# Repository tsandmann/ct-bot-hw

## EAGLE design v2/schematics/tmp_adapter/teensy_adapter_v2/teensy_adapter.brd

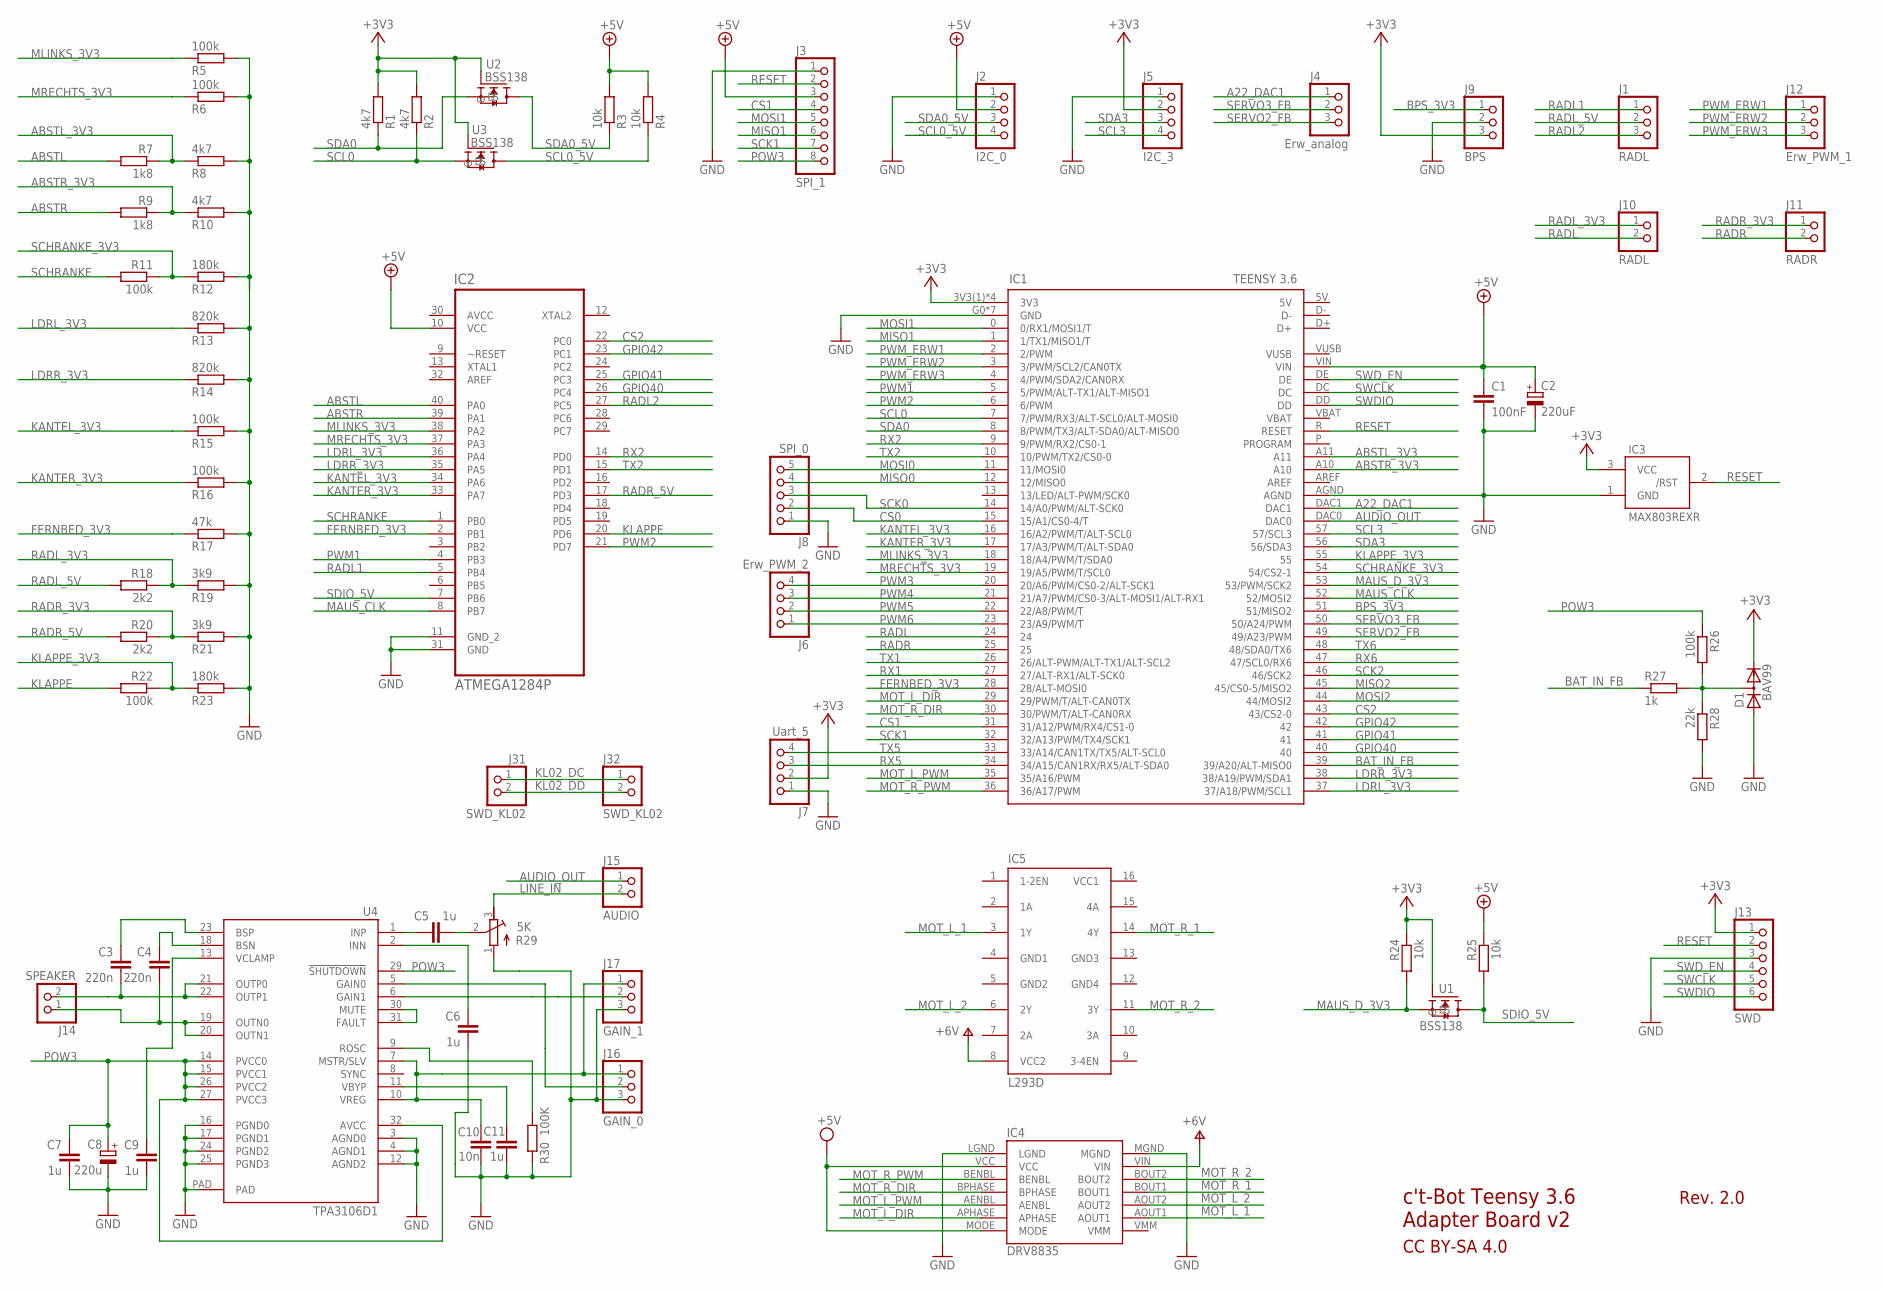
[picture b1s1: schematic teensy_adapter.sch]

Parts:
C1: 100nF; C025-025X050
C2: 220uF; E2,5-6
C3, C4: 220n; C025-025X050
C5, C6, C7, C9, C11: 1u; C025-025X050
C8: 220u; E2,5-6
C10: 10n; C025-025X050
D1: BAV99; SOT23
IC1: TEENSY 3.6; T36
IC2: ATMEGA1284P; DIP254P1524X483-40
IC3: MAX803REXR; SC70-3L
IC4: DRV8835; POLOLU_MOTOR_DRV_DRV8835
IC5: L293D; DIL16
J1: RADL; 1X03
J2: I2C_0; 1X04
J3: SPI_1; 1X08
J4: Erw_analog; 1X03
J5: I2C_3; 1X04
J6: Erw_PWM_2; 1X04
J7: Uart_5; 1X04
J8: SPI_0; 1X05
J9: BPS; 1X03
J10: RADL; 1X02
J11: RADR; 1X02
J12: Erw_PWM_1; 1X03
J13: SWD; 1X06
J14: SPEAKER; 1X02
J15: AUDIO; 1X02
J16: GAIN_0; 1X03
J17: GAIN_1; 1X03
J31: SWD_KL02; 1X02
J32: SWD_KL02; 1X02/90
R1, R2, R8, R10: 4k7; 0204V
R3, R4, R24, R25: 10k; 0204V
R5, R6, R11, R15, R16, R22, R26: 100k; 0204V
R7, R9: 1k8; 0204V
R12, R23: 180k; 0204V
R13, R14: 820k; 0204V
R17: 47k; 0204V
R18, R20: 2k2; 0204V
R19, R21: 3k9; 0204V
R27: 1k; 0204V
R28: 22k; 0204V
R29: 5K; RTRIM64W
R30: 100K; 0204V
U1, U2, U3: BSS138
U4: TPA3106D1; HTQFP32

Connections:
+3V3: D1.2 (C), IC1.3V3(1) (3V3), IC1.3V3(2) (3V3), IC1.3V3(3) (3V3), IC1.3V3(4) (3V3), IC3.3 (VCC), J5.2, J7.2, J9.3, J13.1, R1.2, R2.2, R24.1, U1.G, U2.G, U3.G
+5V: C1.1, C2.+, IC1.VIN, IC2.10 (VCC), IC4.MODE, IC4.VCC, J2.2, J3.3, R3.2, R4.2, R25.1
+6V: IC4.VIN, IC5.8 (VCC2)
A22_DAC1: IC1.DAC1, J4.1
ABSTL: IC2.40 (PA0), R7.2
ABSTL_3V3: IC1.A11, R7.1, R8.1
ABSTR: IC2.39 (PA1), R9.2
ABSTR_3V3: IC1.A10, R9.1, R10.1
AUDIO_OUT: IC1.DAC0, J15.1
AVCC: IC2.30 (AVCC)
BAT_IN_FB: IC1.39 (39/A20/ALT-MISO0), R27.1
BPS_3V3: IC1.51 (51/MISO2), J9.1
BSN: C4.1, U4.18 (BSN)
BSP: C3.1, U4.23 (BSP)
CS0: IC1.15 (15/A1/CS0-4/T), J8.2
CS1: IC1.31 (31/A12/PWM/RX4/CS1-0), J3.4
CS2: IC1.43 (43/CS2-0), IC2.22 (PC0)
FERNBED_3V3: IC1.28 (28/ALT-MOSI0), IC2.2 (PB1), R17.1
GAIN0: J16.2, U4.5 (GAIN0)
GAIN1: J17.2, U4.6 (GAIN1)
GND: C1.2, C2.-, C6.2, C7.2, C8.-, C9.2, C10.2, C11.2, D1.1 (A), IC1.AGND, IC1.G0 (GND), IC1.G1 (GND), IC1.G2 (GND), IC1.G3 (GND), IC1.G4 (GND), IC1.G5 (GND), IC1.G6 (GND), IC2.11 (GND_2), IC2.31 (GND), IC3.1 (GND), IC4.LGND, IC4.MGND, J2.1, J3.1, J5.1, J7.1, J8.1, J9.2, J13.3, J16.3, J17.3, R5.2, R6.2, R8.2, R10.2, R12.2, R13.2, R14.2, R15.2, R16.2, R17.2, R19.2, R21.2, R23.2, R28.2, R29.1 (E), R30.1, U4.3 (AGND0), U4.4 (AGND1), U4.12 (AGND2), U4.16 (PGND0), U4.17 (PGND1), U4.24 (PGND2), U4.25 (PGND3), U4.PAD
GND1: IC5.4 (GND1)
GND2: IC5.5 (GND2)
GND3: IC5.13 (GND3)
GND4: IC5.12 (GND4)
GPIO40: IC1.40, IC2.26 (PC4)
GPIO41: IC1.41, IC2.25 (PC3)
GPIO42: IC1.42, IC2.23 (PC1)
INN: C6.1, U4.2 (INN)
INP: C5.1, U4.1 (INP)
KANTEL_3V3: IC1.16 (16/A2/PWM/T/ALT-SCL0), IC2.34 (PA6), R15.1
KANTER_3V3: IC1.17 (17/A3/PWM/T/ALT-SDA0), IC2.33 (PA7), R16.1
KL02_DC: J31.1, J32.1
KL02_DD: J31.2, J32.2
KLAPPE: IC2.20 (PD6), R22.2
KLAPPE_3V3: IC1.55, R22.1, R23.1
LDRL_3V3: IC1.37 (37/A18/PWM/SCL1), IC2.36 (PA4), R13.1
LDRR_3V3: IC1.38 (38/A19/PWM/SDA1), IC2.35 (PA5), R14.1
LINE_IN: J15.2, R29.3 (A)
MAUS_CLK: IC1.52 (52/MOSI2), IC2.8 (PB7)
MAUS_D_3V3: IC1.53 (53/PWM/SCK2), R24.2, U1.S
MISO0: IC1.12 (12/MISO0), J8.4
MISO1: IC1.1 (1/TX1/MISO1/T), J3.6
MISO2: IC1.45 (45/CS0-5/MISO2)
MLINKS_3V3: IC1.18 (18/A4/PWM/T/SDA0), IC2.38 (PA2), R5.1
MOSI0: IC1.11 (11/MOSI0), J8.5
MOSI1: IC1.0 (0/RX1/MOSI1/T), J3.5
MOSI2: IC1.44 (44/MOSI2)
MOT_L_1: IC4.AOUT1, IC5.3 (1Y)
MOT_L_2: IC4.AOUT2, IC5.6 (2Y)
MOT_L_DIR: IC1.29 (29/PWM/T/ALT-CAN0TX), IC4.APHASE
MOT_L_PWM: IC1.35 (35/A16/PWM), IC4.AENBL
MOT_R_1: IC4.BOUT1, IC5.14 (4Y)
MOT_R_2: IC4.BOUT2, IC5.11 (3Y)
MOT_R_DIR: IC1.30 (30/PWM/T/ALT-CAN0RX), IC4.BPHASE
MOT_R_PWM: IC1.36 (36/A17/PWM), IC4.BENBL
MRECHTS_3V3: IC1.19 (19/A5/PWM/T/SCL0), IC2.37 (PA3), R6.1
unnamed: D1.3 (AC), R26.2, R27.2, R28.1
unnamed: U4.30 (MUTE), U4.31 (FAULT)
unnamed: C5.2, R29.2 (S)
OUTN: C4.2, J14.1, U4.19 (OUTN0), U4.20 (OUTN1)
OUTP: C3.2, J14.2, U4.21 (OUTP0), U4.22 (OUTP1)
POW3: C7.1, C8.+, J3.8, R26.1, U4.14 (PVCC0), U4.15 (PVCC1), U4.26 (PVCC2), U4.27 (PVCC3), U4.29 (!SHUTDOWN), U4.32 (AVCC)
PWM1: IC1.5 (5/PWM/ALT-TX1/ALT-MISO1), IC2.4 (PB3)
PWM2: IC1.6 (6/PWM), IC2.21 (PD7)
PWM3: IC1.20 (20/A6/PWM/CS0-2/ALT-SCK1), J6.4
PWM4: IC1.21 (21/A7/PWM/CS0-3/ALT-MOSI1/ALT-RX1), J6.3
PWM5: IC1.22 (22/A8/PWM/T), J6.2
PWM6: IC1.23 (23/A9/PWM/T), J6.1
PWM_ERW1: IC1.2 (2/PWM), J12.1
PWM_ERW2: IC1.3 (3/PWM/SCL2/CAN0TX), J12.2
PWM_ERW3: IC1.4 (4/PWM/SDA2/CAN0RX), J12.3
RADL: IC1.24, J10.2
RADL1: IC2.5 (PB4), J1.1
RADL2: IC2.27 (PC5), J1.3
RADL_3V3: J10.1, R18.1, R19.1
RADL_5V: J1.2, R18.2
RADR: IC1.25, J11.2
RADR_3V3: J11.1, R20.1, R21.1
RADR_5V: IC2.17 (PD3), R20.2
RESET: IC1.R (RESET), IC3.2 (/RST), J3.2, J13.2
ROSC: R30.2, U4.9 (ROSC)
RX1: IC1.27 (27/ALT-RX1/ALT-SCK0)
RX2: IC1.9 (9/PWM/RX2/CS0-1), IC2.14 (PD0)
RX5: IC1.34 (34/A15/CAN1RX/RX5/ALT-SDA0), J7.3
RX6: IC1.47 (47/SCL0/RX6)
SCHRANKE: IC2.1 (PB0), R11.2
SCHRANKE_3V3: IC1.54 (54/CS2-1), R11.1, R12.1
SCK0: IC1.14 (14/A0/PWM/ALT-SCK0), J8.3
SCK1: IC1.32 (32/A13/PWM/TX4/SCK1), J3.7
SCK2: IC1.46 (46/SCK2)
SCL0: IC1.7 (7/PWM/RX3/ALT-SCL0/ALT-MOSI0), R2.1, U3.S
SCL0_5V: J2.4, R4.1, U3.D
SCL3: IC1.57 (57/SCL3), J5.4
SDA0: IC1.8 (8/PWM/TX3/ALT-SDA0/ALT-MISO0), R1.1, U2.S
SDA0_5V: J2.3, R3.1, U2.D
SDA3: IC1.56 (56/SDA3), J5.3
SDIO_5V: IC2.7 (PB6), R25.2, U1.D
SERVO2_FB: IC1.49 (49/A23/PWM), J4.3
SERVO3_FB: IC1.50 (50/A24/PWM), J4.2
SWCLK: IC1.DC, J13.5
SWDIO: IC1.DD, J13.6
SWD_EN: IC1.DE, J13.4
TX1: IC1.26 (26/ALT-PWM/ALT-TX1/ALT-SCL2)
TX2: IC1.10 (10/PWM/TX2/CS0-0), IC2.15 (PD1)
TX5: IC1.33 (33/A14/CAN1TX/TX5/ALT-SCL0), J7.4
TX6: IC1.48 (48/SDA0/TX6)
VBYP: C11.1, U4.11 (VBYP)
VCC1: IC5.16 (VCC1)
VCLAMP: C9.1, U4.13 (VCLAMP)
VREG: C10.1, J16.1, J17.1, U4.7 (MSTR/SLV), U4.10 (VREG)

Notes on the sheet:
c't-Bot Teensy 3.6 Adapter Board v2
Rev. 2.0
CC BY-SA 4.0

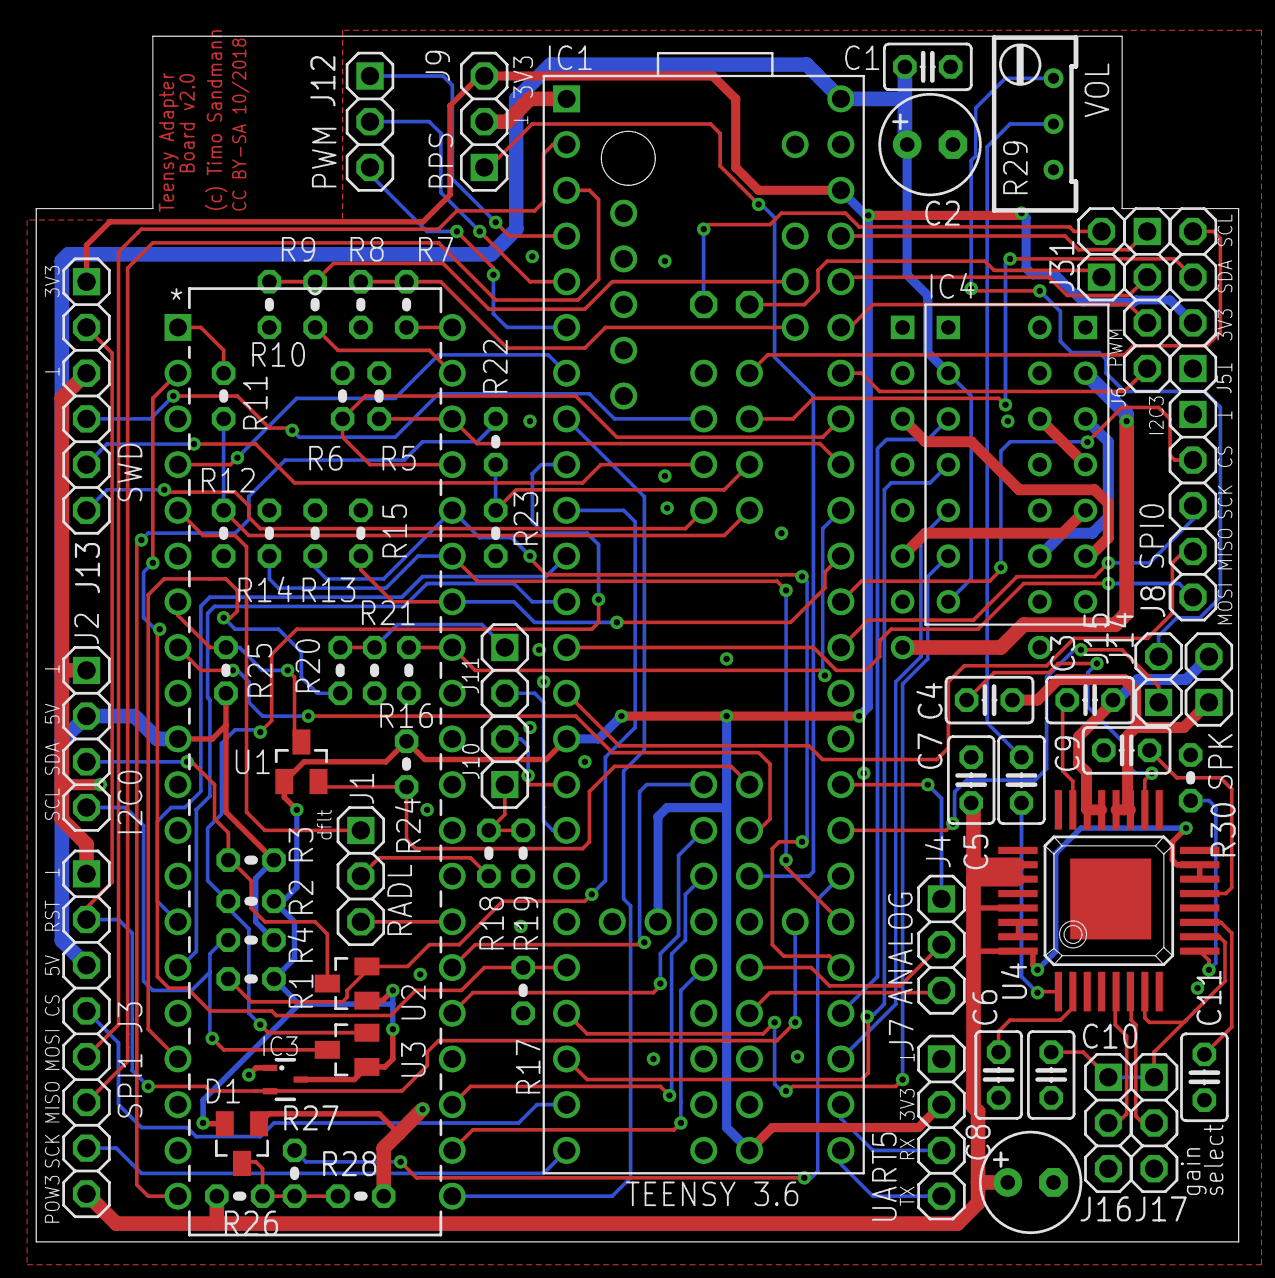
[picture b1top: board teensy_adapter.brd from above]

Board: 2 copper layers, 66.8 x 67.0 mm, 70 parts (1 on the bottom side), 98 nets.

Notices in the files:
v2/schematics/tmp_adapter/teensy_adapter_v2/teensy_adapter.brd:
CC BY-SA 10/2018
